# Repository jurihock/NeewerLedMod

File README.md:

# Neewer LED panel modification

Homemade Arduino Nano based driver for the [Neewer BP300](https://neewer.com/products/neewer-bp300-2-pack-led-video-light-panel-lighting-kit-66606584) LED panel.

## Features

- Single controller to sync two LED panels
- Color balance between cool and warm
- Brightness balance between two LED panels
- Total brightness adjustment

## Implementation

- Basically PWM followed by a logic-level MOSFET, e.g. IRLZ44N
- Utilizing timers 1 and 2 of the [ATmega328](https://en.wikipedia.org/wiki/ATmega328) chip to generate 2x2 PWM signals up to ~60kHz common frequency and individual duty cycles

### See also

- [The MOSFET as Switch](https://wolles-elektronikkiste.de/en/the-mosfet-as-switch)

## Details

### PSU

- [LEICKE ULL 5V 8A](https://www.leicke.de/shop-artikel/buero/leicke-ull-netzteil-40w-5v-8a_106522_67199) or [6A](https://www.leicke.de/shop-artikel/buero/leicke-ull-netzteil-30w-5v-6a_106544_67223)
- Connector 5.5x2.5mm (+)
- Actually 5.5V **not** 5.0V output voltage
- Audible noise below 7W load
- [Meanwell GST60A05-P1J 5V 6A](https://www.welectron.com/Meanwell-GST60A05-P1J-Desktop-Power-Supply-5V-6A) or [medical](https://www.reichelt.de/de/de/shop/produkt/steckernetzteil_30_w_5_v_6_a_medical-386168) as possible alternative

### MCU

- [Arduino Nano compatible clone](https://www.christians-shop.de/nano-v3-0-atmega328p-development-board-without-soldering-christians-technikshop)
- Fittingly VIN between 5V and 12V
- Otherwise [Pololu S7V8F5](https://www.pololu.com/product/2123)

### Wiring

- Extension cable [LiYY 3x0.34mm²](https://www.ebay.de/itm/325896583886)
- Cable connector [M13 5A](https://www.ebay.de/itm/323694504483)

| Label  | Native wire | Extension wire | Connector pin |
|--------|-------------|----------------|---------------|
| W-     | Yellow      | Green          | 1             |
| C-     | Black       | White          | 2             |
| + (5V) | Red         | Brown          | 3             |

### LED indicators

| Color | Resistor |
|-------|----------|
| G     | 470      |
| R     | 2k       |
| B     | 10k      |

### Pots

- 3x10k

### Fuses

- 2x3A slow or fast

### Housing

- [TEKO 362](https://www.teko.it/en/products/family/PU/series/pult-36) or similar

## How it looks like

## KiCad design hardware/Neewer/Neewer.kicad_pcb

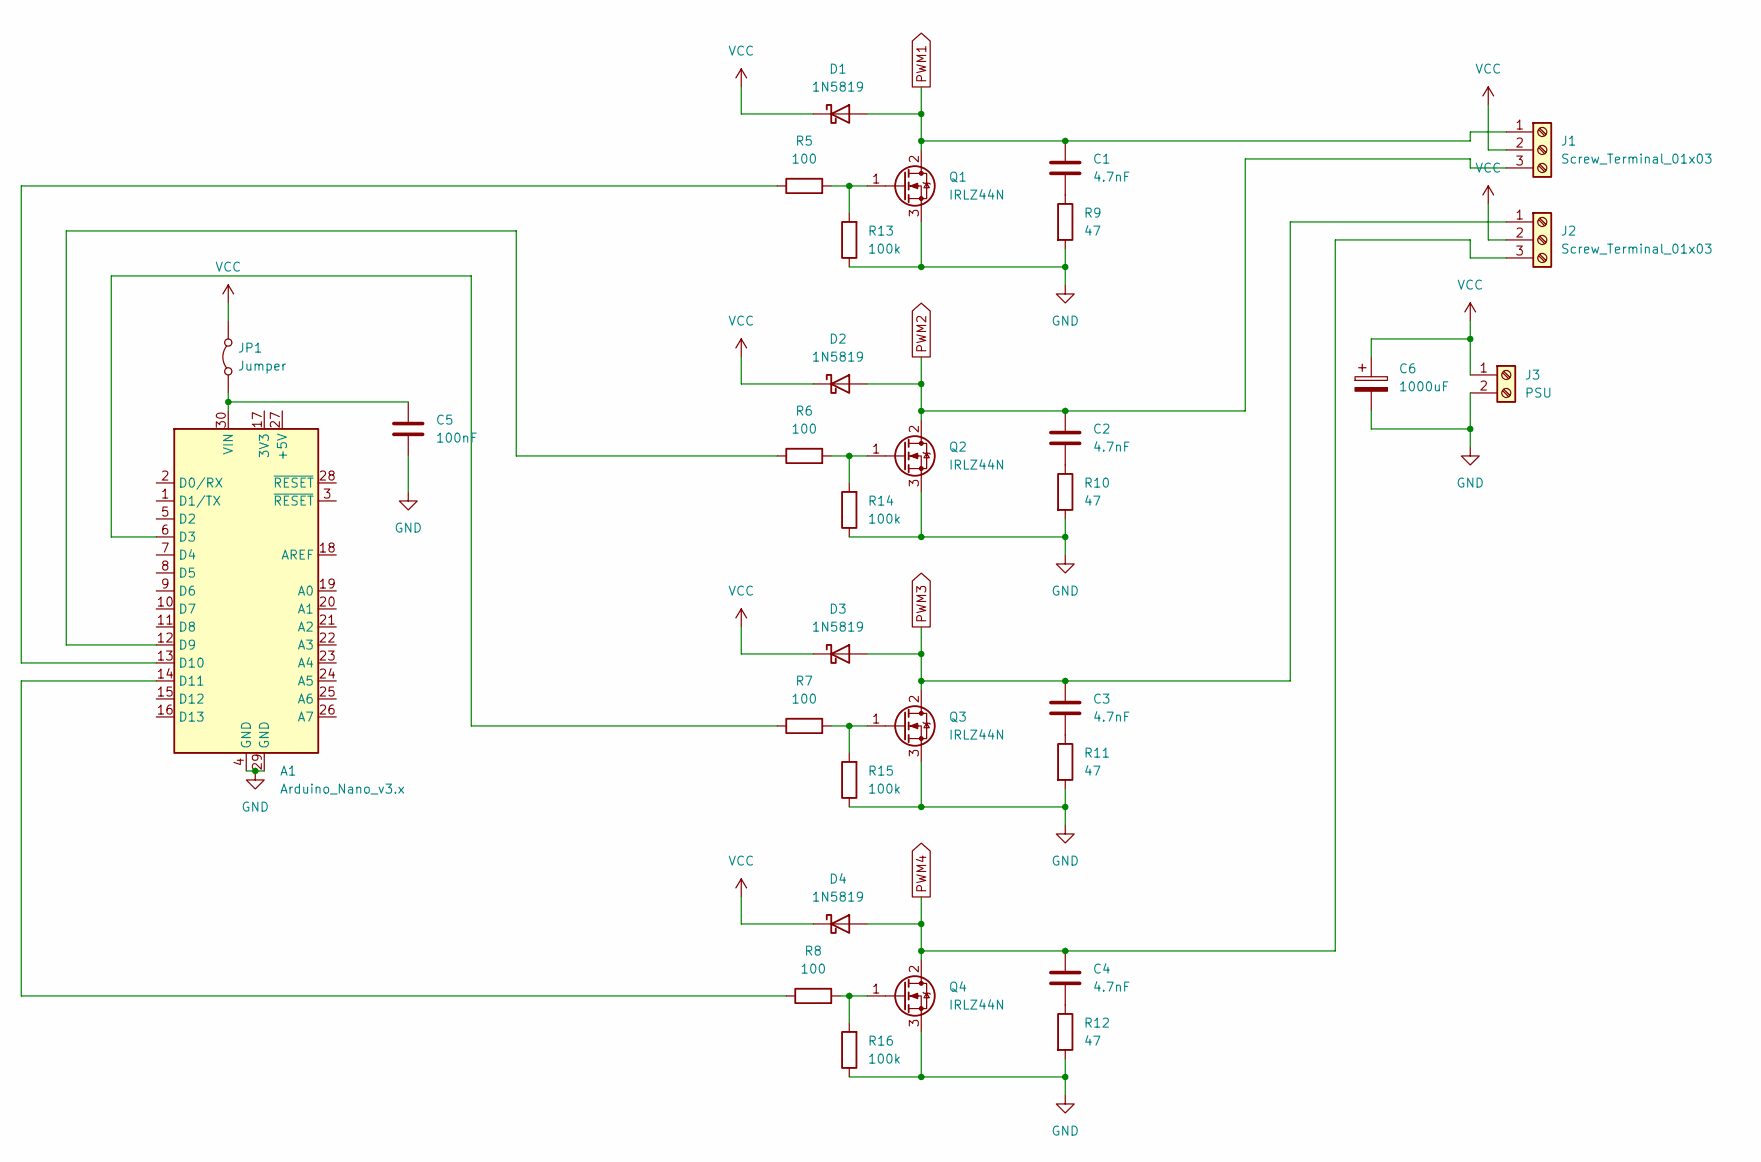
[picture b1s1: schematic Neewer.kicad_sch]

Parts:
A1: Arduino_Nano_v3.x; Arduino_Nano
C1, C2, C3, C4: 4.7nF; C_Disc_D5.0mm_W2.5mm_P2.50mm
C5: 100nF; C_Disc_D5.0mm_W2.5mm_P2.50mm
C6: 1000uF; CP_Radial_D13.0mm_P5.00mm
D1, D2, D3, D4: 1N5819; D_DO-41_SOD81_P5.08mm_Vertical_AnodeUp
J1, J2: Screw_Terminal_01x03; TerminalBlock_MetzConnect_Type055_RT01503HDWU_1x03_P5.00mm_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
J3: PSU; TerminalBlock_MetzConnect_Type055_RT01502HDWU_1x02_P5.00mm_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
JP1: Jumper; TestPoint_2Pads_Pitch2.54mm_Drill0.8mm
Q1, Q2, Q3, Q4: IRLZ44N; TO-220-3_Vertical
R5, R6, R7, R8: 100; R_Axial_DIN0207_L6.3mm_D2.5mm_P15.24mm_Horizontal
R9, R10, R11, R12: 47; R_Axial_DIN0207_L6.3mm_D2.5mm_P2.54mm_Vertical
R13, R14, R15, R16: 100k; R_Axial_DIN0207_L6.3mm_D2.5mm_P2.54mm_Vertical

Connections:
GND: A1.4 (GND), A1.29 (GND), C5.2, C6.2, J3.2, Q1.3 (S), Q2.3 (S), Q3.3 (S), Q4.3 (S), R9.2, R10.2, R11.2, R12.2, R13.1, R14.1, R15.1, R16.1
unnamed: A1.6 (D3), R7.1
unnamed: A1.12 (D9), R6.1
unnamed: A1.13 (D10), R5.1
unnamed: A1.14 (D11), R8.1
unnamed: A1.30 (VIN), C5.1, JP1.1 (A)
unnamed: C1.2, R9.1
unnamed: C2.2, R10.1
unnamed: C3.2, R11.1
unnamed: C4.2, R12.1
unnamed: Q1.1 (G), R5.2, R13.2
unnamed: Q2.1 (G), R6.2, R14.2
unnamed: Q3.1 (G), R7.2, R15.2
unnamed: Q4.1 (G), R8.2, R16.2
PWM1: C1.1, D1.2 (A), J1.1, Q1.2 (D)
PWM2: C2.1, D2.2 (A), J1.3, Q2.2 (D)
PWM3: C3.1, D3.2 (A), J2.1, Q3.2 (D)
PWM4: C4.1, D4.2 (A), J2.3, Q4.2 (D)
VCC: C6.1, D1.1 (K), D2.1 (K), D3.1 (K), D4.1 (K), J1.2, J2.2, J3.1, JP1.2 (B)

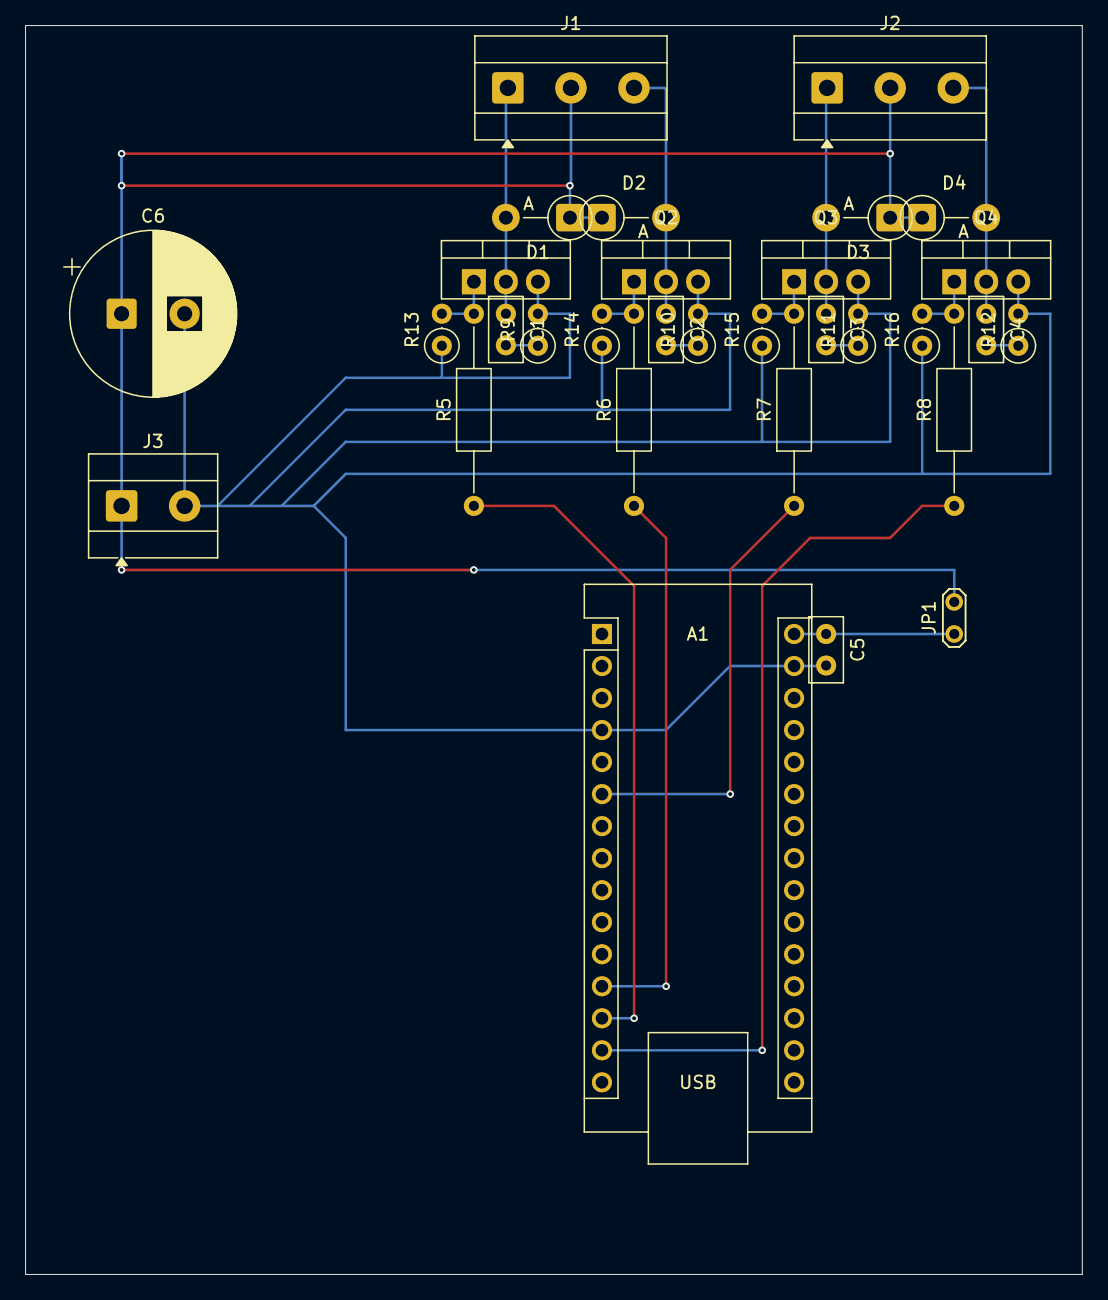
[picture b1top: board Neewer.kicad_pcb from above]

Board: 2 copper layers, 83.8 x 99.1 mm, 31 parts (0 on the bottom side), 19 nets.

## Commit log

2026-04-27 Add source files
2026-04-27 Add link to Neewer BP300 in README
2026-04-27 Force PWM outputs to go LOW at the boundary
2026-04-27 Update kicad
2026-04-27 Add housing cover
2026-04-27 Update assets
2026-04-28 Add initial ramp
2026-04-28 Fix setup order
2026-04-28 Add housing appearance section with image
    Added a section on how the housing looks with an image.
2026-04-28 Fix image path in README.md
2026-04-28 Update alternative power supply options in README
